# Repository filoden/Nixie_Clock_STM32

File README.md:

# Nixie_Clock_STM32

An STM32-based **Nixie-tube alarm clock** (HH:MM) with audio, SD storage, and a custom enclosure. 
Repository still in developement.

> ⚠️ **High Voltage Warning**
> Nixie tubes require a high-voltage supply (~170VDC for IN-12 used in this project). Basic HV safety knowledge is necessary to avoid injury and or death.

---

## Project Snapshot

**Design tools:** KiCad (PCB), STM32CubeMX / STM32CubeIDE (firmware), SolidWorks (enclosure)

**Repo structure**
- `Current Iteration/` – active hardware + firmware
  - `Current Iteration/Enclosure`
  - `Current Iteration/STM32 Project Files and Code`
  - `Current Iteration/Schematic Layout & PCB`
- `Old_Versions/` – previous spins / archived work

---

## Features

### Hardware / Electronics (status)
**In development**
- low power / battery-power mode
- Oscillator bring-up / stability checks

**Tested (prototype version)**
- Capacitive touch input

**Finalized**
- I2S audio communication
- 5V → 12V boost 
- SPI / I2C communication
- SD Card Interface
- Rotary encoders
- 5V → 3.3V LDO
- Audio output: driving a 4Ω speaker through the MAX98567A (except for bulk cap)
- SD audio file reading

---

## Hardware Overview (high level)

- **MCU:** STM32G0B1RETx6
- **UX/UI:** rotary encoder(s) (One encouder includes a push button), capacitive touch
- **Timekeeping:** STM32 RTC + external LSE oscillator
- **Storage:** microSD over SPI (FatFs)
- **Audio:** I2S to class-D amp (MAX98567A) → 4Ω speaker
- **Driving Nixie Tubes** STM MCU drives serial into a 12V level shifter which drives HV5622PG chips. These chips switch the tubes using an external 170V DC source.
- **Capacitive touch senor** Conductive edge banding surrounds large portions of controller. CAP1206 IC interprets changes in banding capacitance and communicates over I2C to MCU.
- **Power:**
  - USB-C 5V input (mechanical + ESD considerations)
  - 5V enters Linear low-dropout regulator -> 3.3V 
  - 3.3V rail for logic
  - HV rail for Nixie tubes (external boost converter)
  - Battery backup is used for logic, oscillator, amplifier, and capacitive touch sensor in the event of 5V loss
  - Battery and 3.3V power is controlled using NID5100, low-forward voltage drop diodes.
### Schematic Preview

### Block Diagram

#### Notes:
- All Power lines are written in red text
- Arrow direction denotes either flow of power or data (although JTAG should be bidirectional)
- Ground for IN12 Tubes is omitted
---

## Firmware 
### Build / Flash 
1. Open the firmware project in **STM32CubeIDE**.
2. Confirm CubeMX-generated peripherals match the board wiring (SPI for SD, I2S for audio, GPIO/EXTI for inputs). Make sure to include separate driver files for FATFS (Provided by CubeMX). 
4. Build + flash via **ST-LINK**.
5. To avoid frustration, bring-up in this order:
### Firmware Development (Status):
### Integration:
**1. UI FSM**
- UI is structured as an FSM. Programmatically each input will trigger a user-input function for each respective input (knob A turns CC, knob B turns C, etc.. Each function consists of a long switch case which maps the appropriate response to an input for a given state. Relevant code is in UserInterface source and header files. FSM can be seen below.

**Notes to come:**

**2. DMA music playing**

**3. SD card interface**

**4. Capacitive touch sensor**

**5. Music FIle Parsing**

### In development:

**6. Nixie driver control logic**

- Nixie tubes require 170VDC switching. Thankfully, Many old display tubes and other vintage electronics require high voltage DC. Since there is still demand for this technology an old (relatively speaking) serial to parallel high voltage switching IC known as the HV5622PG is still in production. This $8 chip can handle up to 250VDC and requires a ridiculous 12V logic level. The Nixie driver control logic tells this chip which digits to turn on. Importantly, it must also make sure that no more than one digit is driven at a time, as this can easily destroy the tube. Additionally, it is necesary to include PWM control to allow for dimming, and to be easily accessible by other parts of the code.
- Requirements: 
  - Checks to ensure there is no double digit driving
  - Dimming Control
  - Simple function call

**7. Low-Power (Blackout) Handling**

Requirements:
  - Set Pins to LOW (Remove any Pullups as well): Nixie Driving GPIO, JTAG, SD_CARD, CAP1206, knobs B/C
  - Following Interfaces to remain as normal: MAX98357A
  - Sense Power-outage via ST pin on NID5100
  - Be able to play low power alarm song stored solely in on-chip memory

**8. New external LSE with RTC implementation**

Requirements:
  - Initialization
  - Maintain RTC control through momentary resets
  - Calibration (?)
---

## PCB Development
Current version consists of a single main board with three separate smaller boards (separated by user) for the rotary encoder circuitry.
- **V1 PCB:** learning spin (many layout mistakes)
- **V2 PCB:** More fully built out, includes all relevent IO.
- **V3 PCB:** pending completion of wiring/programming development - most up to date version located in current iteration. 
### To-do
- External LSE oscillator testing
- Add AA discharge protection
- Connext NCH6100HV Directly to 5V rail instead of 12V
- Much more
### PCB Preview
**V3 PCB:**
 
---

## Enclosure Development

### Current plan
- Mostly **wood** enclosure in **two glued halves**
- Two halves are **mostly symmetric** and CNC-machinable from a single board  
  - Best results: mill one thick piece and split for mirrored grain (book-matching)
- **Front + back edges:** laser-cut **aluminum edge banding** (strength + aesthetics), glued in place
- **Back plate:** thicker aluminum for rotary encoders + USB-C inlet
- **Front plate:** 1/8" glass (waterjet preferred; hand-fab possible) with a grey tint

### To-do
- Vector files: back plate, glass face, edge banding
- Finalize BOM
- Investigate use of waterjet for glass face
### Enclosure Preview

---

## BOM
- PCB BOM currently matches latest revision
- Enclosure BOM is out of date

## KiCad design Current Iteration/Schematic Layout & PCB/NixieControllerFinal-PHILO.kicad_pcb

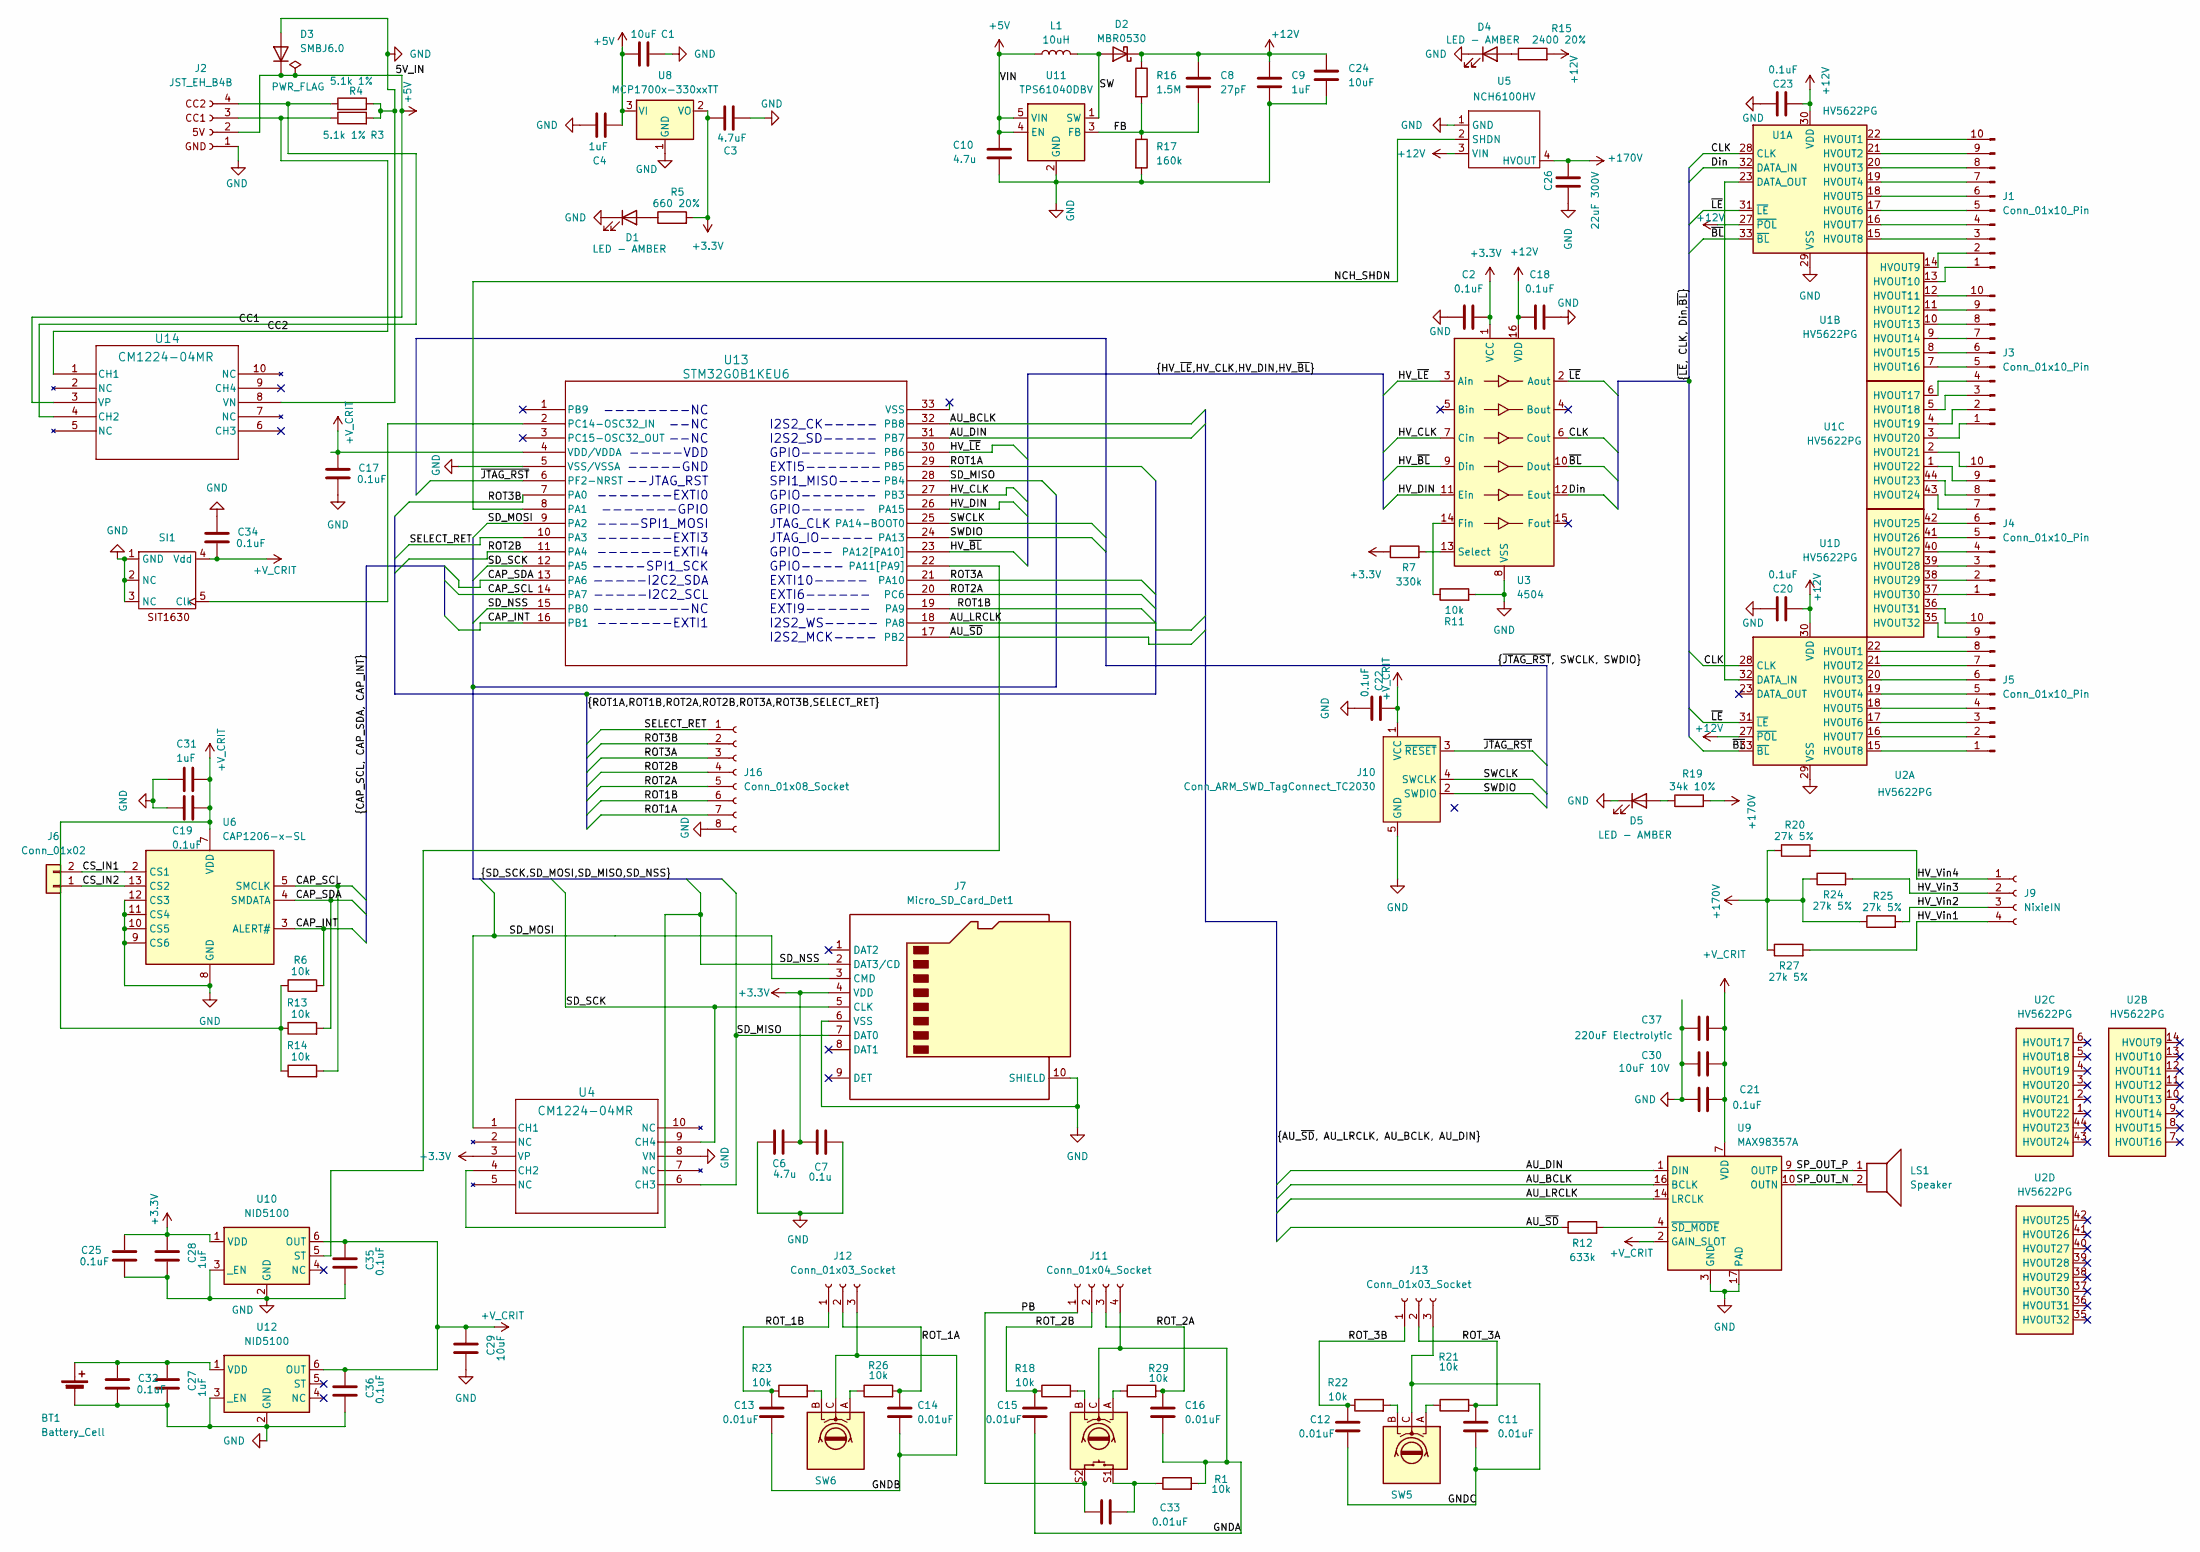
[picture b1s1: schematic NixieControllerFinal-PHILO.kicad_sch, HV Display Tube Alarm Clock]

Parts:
BT1: Battery_Cell; JST_EH_B2B-EH-A_1x02_P2.50mm_Vertical
C1, C24: 10uF; C_0805_2012Metric_Pad1.18x1.45mm_HandSolder
C2, C17, C18, C20, C21, C23, C25, C32, C35, C36: 0.1uF; C_0603_1608Metric_Pad1.08x0.95mm_HandSolder
C3: 4.7uF; C_0805_2012Metric_Pad1.18x1.45mm_HandSolder
C4, C9, C27, C28, C31: 1uF; C_0805_2012Metric_Pad1.18x1.45mm_HandSolder
C6, C10: 4.7u; C_0805_2012Metric_Pad1.18x1.45mm_HandSolder
C7: 0.1u; C_0603_1608Metric_Pad1.08x0.95mm_HandSolder
C8: 27pF; C_0603_1608Metric_Pad1.08x0.95mm_HandSolder
C11, C12, C13, C14, C15, C16, C33: 0.01uF; C_0805_2012Metric_Pad1.18x1.45mm_HandSolder
C19, C22, C34: 0.1uF; C_0805_2012Metric_Pad1.18x1.45mm_HandSolder
C26: 22uF 300V; CP_Radial_D8.0mm_P3.50mm
C29: 10uF; C_1206_3216Metric_Pad1.33x1.80mm_HandSolder
C30: 10uF 10V; C_0603_1608Metric_Pad1.08x0.95mm_HandSolder
C37: 220uF Electrolytic; CP_Radial_D5.0mm_P2.00mm
D1, D4, D5: 150060AS75000; LED_0603_1608Metric_Pad1.05x0.95mm_HandSolder
D2: MBR0530; D_SOD-123
D3: SMBJ6.0; D_SMB
J1, J3, J4, J5: Conn_01x10_Pin; JST_SH_BM10B-SRSS-TB_1x10-1MP_P1.00mm_Vertical
J2: JST_EH_B4B; JST_EH_B4B-EH-A_1x04_P2.50mm_Vertical
J6: Conn_01x02; JST_PH_B2B-PH-K_1x02_P2.00mm_Vertical
J7: Micro_SD_Card_Det1; microSD_HC_Molex_104031-0811
J9: NixieIN; JST_SH_BM04B-SRSS-TB_1x04-1MP_P1.00mm_Vertical
J10: Conn_ARM_SWD_TagConnect_TC2030; PinHeader_1x05_P2.54mm_Vertical
J11: Conn_01x04_Socket; JST_SH_BM04B-SRSS-TB_1x04-1MP_P1.00mm_Vertical
J12, J13: Conn_01x03_Socket; JST_SH_BM03B-SRSS-TB_1x03-1MP_P1.00mm_Vertical
J16: Conn_01x08_Socket; JST_SH_BM08B-SRSS-TB_1x08-1MP_P1.00mm_Vertical
L1: 10uH; L_0805_2012Metric_Pad1.05x1.20mm_HandSolder
LS1: Speaker; JST_PH_B2B-PH-K_1x02_P2.00mm_Vertical
R1, R6, R11, R13, R14, R18, R21, R22, R23, R26, R29: 10k; R_0805_2012Metric_Pad1.20x1.40mm_HandSolder
R3, R4: 5.1k 1%; R_0805_2012Metric_Pad1.20x1.40mm_HandSolder
R5: 660 20%; R_0805_2012Metric_Pad1.20x1.40mm_HandSolder
R7: 330k; R_0805_2012Metric_Pad1.20x1.40mm_HandSolder
R12: 633k; R_0805_2012Metric_Pad1.20x1.40mm_HandSolder
R15: 2400 20%; R_0805_2012Metric_Pad1.20x1.40mm_HandSolder
R16: 1.5M; R_0603_1608Metric_Pad0.98x0.95mm_HandSolder
R17: 160k; R_0603_1608Metric_Pad0.98x0.95mm_HandSolder
R19: 34k 10%; R_1206_3216Metric_Pad1.30x1.75mm_HandSolder
R20, R24, R25, R27: 27k 5%; R_0805_2012Metric_Pad1.20x1.40mm_HandSolder
SI1: SOT-23-5_HandSoldering
SW1, SW5, SW6: RotaryEncoder_Bourns_Vertical_PEC12R-3x17F-Sxxxx
U1, U2: HV5622PG; PQFP-44_10x10mm_P0.8mm
U3: 4504; SOIC-16_ONS
U4, U14: CM1224-04MR; TSSOP-10_3x3mm_P0.5mm
U5: NCH6100HV; JST_EH_B4B-EH-A_1x04_P2.50mm_Vertical
U6: CAP1206-x-SL; SOIC-14_3.9x8.7mm_P1.27mm
U8: MCP1700x-330xxTT; SOT-23
U9: MAX98357A; TQFN-16-1EP_3x3mm_P0.5mm_EP1.23x1.23mm
U10, U12: NID5100; SC-74-6_1.55x2.9mm_P0.95mm
U11: TPS61040DBV; SOT-23-5
U13: STM32G0B1KEU6; UFQFPN-32-1EP_5x5mm_P0.5mm_EP3.5x3.5mm

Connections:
+3.3V: C2.2, C3.1, C6.1, C7.2, C25.1, C28.1, J7.4 (VDD), R5.2, R7.1, U3.1 (VCC), U4.3 (VP), U8.2 (VO), U10.1 (VDD)
+5V: C1.1, C4.1, C10.1, D3.1 (K), J2.2 (5V), L1.1, U8.3 (VI), U11.4 (EN), U11.5 (VIN), U14.3 (VP)
+12V: C8.1, C9.1, C18.1, C20.1, C23.1, C24.1, D2.1 (K), R15.2, R16.1, U1.27 (~POL), U1.30 (VDD), U2.27 (~POL), U2.30 (VDD), U3.16 (VDD), U5.3 (VIN)
+170V: C26.1, R19.2, R20.1, R24.1, R25.1, R27.1, U5.4 (HVOUT)
+V_CRIT: C17.1, C19.1, C21.1, C22.1, C29.1, C30.1, C31.1, C34.2, C35.1, C36.1, C37.1, J10.1 (VCC), R6.1, R13.1, R14.1, SI1.4 (Vdd), U6.7 (VDD), U9.2 (GAIN_SLOT), U9.7 (VDD), U9.8 (VDD), U10.6 (OUT), U12.6 (OUT), U13.4 (VDD/VDDA)
/AU_BCLK: U9.16 (BCLK), U13.32 (PB8)
/AU_DIN: U9.1 (DIN), U13.31 (PB7)
/AU_LRCLK: U9.14 (LRCLK), U13.18 (PA8)
/AU_~SD: R12.1, U13.17 (PB2)
/CAP_INT: R6.2, U6.3 (ALERT#), U13.16 (PB1)
/CAP_SCL: R14.2, U6.5 (SMCLK), U13.14 (PA7)
/CAP_SDA: R13.2, U6.4 (SMDATA), U13.13 (PA6)
/CC1: J2.4 (CC2), R4.1, U14.4 (CH2)
/CC2: J2.3 (CC1), R3.1, U14.1 (CH1)
/CLK: U1.28 (CLK), U2.28 (CLK), U3.6 (Cout)
/CS_IN1: J6.2, U6.2 (CS1)
/CS_IN2: J6.1, U6.13 (CS2)
/Din: U1.32 (DATA_IN), U3.12 (Eout)
/FB: C8.2, R16.2, R17.1, U11.3 (FB)
/GNDA: C15.2, C16.2, J11.4, R1.2, SW1.C
/GNDB: C13.2, C14.2, J12.3, SW6.C
/GNDC: C11.2, C12.2, J13.3, SW5.C
/HV_CLK: U3.7 (Cin), U13.27 (PB3)
/HV_DIN: U3.11 (Ein), U13.26 (PA15)
/HV_Vin1: J9.4, R27.2
/HV_Vin2: J9.3, R25.2
/HV_Vin3: J9.2, R24.2
/HV_Vin4: J9.1, R20.2
/HV_~BL: U3.9 (Din), U13.23 (PA12[PA10])
/HV_~LE: U3.3 (Ain), U13.30 (PB6)
/NCH_SHDN: U5.2 (SHDN), U13.8 (PA1)
/PB: C33.1, J11.1, SW1.S2
/ROT1A: J16.7, U13.29 (PB5)
/ROT1B: J16.6, U13.19 (PA9)
/ROT2A: J16.5, U13.20 (PC6)
/ROT2B: J16.4, U13.11 (PA4)
/ROT3A: J16.3, U13.21 (PA10)
/ROT3B: J16.2, U13.7 (PA0)
/ROT_1A: C14.1, J12.2, R26.2
/ROT_1B: C13.1, J12.1, R23.1
/ROT_2A: C16.1, J11.3, R29.2
/ROT_2B: C15.1, J11.2, R18.1
/ROT_3A: C11.1, J13.2, R21.2
/ROT_3B: C12.1, J13.1, R22.1
/SD_MISO: J7.7 (DAT0), U4.6 (CH3), U13.28 (PB4)
/SD_MOSI: J7.3 (CMD), U4.1 (CH1), U13.9 (PA2)
/SD_NSS: J7.2 (DAT3/CD), U4.4 (CH2), U13.15 (PB0)
/SD_SCK: J7.5 (CLK), U4.9 (CH4), U13.12 (PA5)
/SELECT_RET: J16.1, U13.10 (PA3)
/SP_OUT_N: LS1.2, U9.10 (OUTN)
/SP_OUT_P: LS1.1, U9.9 (OUTP)
/SW: D2.2 (A), L1.2, U11.1 (SW)
/SWCLK: J10.4 (SWCLK), U13.25 (PA14-BOOT0)
/SWDIO: J10.2 (SWDIO), U13.24 (PA13)
/~BL: U1.33 (~BL), U2.33 (~BL), U3.10 (Dout)
/~JTAG_RST: J10.3 (~RESET), U13.6 (PF2-NRST)
/~LE: U1.31 (~LE), U2.31 (~LE), U3.2 (Aout)
GND: BT1.2 (-), C1.2, C2.1, C3.2, C4.2, C6.2, C7.1, C9.2, C10.2, C17.2, C18.2, C19.2, C20.2, C21.2, C22.2, C23.2, C24.2, C25.2, C26.2, C27.2, C28.2, C29.2, C30.2, C31.2, C32.2, C34.1, C35.2, C36.2, C37.2, D1.1 (K), D3.2 (A), D4.1 (K), D5.1 (K), J2.1 (GND), J7.6 (VSS), J7.10 (SHIELD), J10.5 (GND), J16.8, R3.2, R4.2, R11.2, R17.2, SI1.1 (GND), SI1.2 (NC), SI1.3 (NC), U1.29 (VSS), U2.29 (VSS), U3.8 (VSS), U4.8 (VN), U5.1 (GND), U6.8 (GND), U6.9 (CS6), U6.10 (CS5), U6.11 (CS4), U6.12 (CS3), U8.1 (GND), U9.3 (GND), U9.11 (GND), U9.15 (GND), U9.17 (PAD), U10.2 (GND), U10.3 (_EN), U11.2 (GND), U12.2 (GND), U12.3 (_EN), U13.5 (VSS/VSSA), U14.8 (VN)
unnamed: BT1.1 (+), C27.1, C32.1, U12.1 (VDD)
unnamed: C33.2, R1.1, SW1.S1
unnamed: D1.2 (A), R5.1
unnamed: D4.2 (A), R15.1
unnamed: D5.2 (A), R19.1
unnamed: J1.1, U1.13 (HVOUT10)
unnamed: J1.2, U1.14 (HVOUT9)
unnamed: J1.3, U1.15 (HVOUT8)
unnamed: J1.4, U1.16 (HVOUT7)
unnamed: J1.5, U1.17 (HVOUT6)
unnamed: J1.6, U1.18 (HVOUT5)
unnamed: J1.7, U1.19 (HVOUT4)
unnamed: J1.8, U1.20 (HVOUT3)
unnamed: J1.9, U1.21 (HVOUT2)
unnamed: J1.10, U1.22 (HVOUT1)
unnamed: J3.1, U1.3 (HVOUT20)
unnamed: J3.2, U1.4 (HVOUT19)
unnamed: J3.3, U1.5 (HVOUT18)
unnamed: J3.4, U1.6 (HVOUT17)
unnamed: J3.5, U1.7 (HVOUT16)
unnamed: J3.6, U1.8 (HVOUT15)
unnamed: J3.7, U1.9 (HVOUT14)
unnamed: J3.8, U1.10 (HVOUT13)
unnamed: J3.9, U1.11 (HVOUT12)
unnamed: J3.10, U1.12 (HVOUT11)
unnamed: J4.1, U1.37 (HVOUT30)
unnamed: J4.2, U1.38 (HVOUT29)
unnamed: J4.3, U1.39 (HVOUT28)
unnamed: J4.4, U1.40 (HVOUT27)
unnamed: J4.5, U1.41 (HVOUT26)
unnamed: J4.6, U1.42 (HVOUT25)
unnamed: J4.7, U1.43 (HVOUT24)
unnamed: J4.8, U1.44 (HVOUT23)
unnamed: J4.9, U1.1 (HVOUT22)
unnamed: J4.10, U1.2 (HVOUT21)
unnamed: J5.1, U2.15 (HVOUT8)
unnamed: J5.2, U2.16 (HVOUT7)
unnamed: J5.3, U2.17 (HVOUT6)
unnamed: J5.4, U2.18 (HVOUT5)
unnamed: J5.5, U2.19 (HVOUT4)
unnamed: J5.6, U2.20 (HVOUT3)
unnamed: J5.7, U2.21 (HVOUT2)
unnamed: J5.8, U2.22 (HVOUT1)
unnamed: J5.9, U1.35 (HVOUT32)
unnamed: J5.10, U1.36 (HVOUT31)
unnamed: R18.2, SW1.B
unnamed: R21.1, SW5.A
unnamed: R22.2, SW5.B
unnamed: R23.2, SW6.B
unnamed: R26.1, SW6.A
unnamed: R29.1, SW1.A
unnamed: SI1.5 (Clk), U13.2 (PC14-OSC32_IN)
unnamed: U1.23 (DATA_OUT), U2.32 (DATA_IN)
unnamed: R11.1, U3.14 (Fin)
unnamed: R7.2, U3.13 (Select)
unnamed: R12.2, U9.4 (~SD_MODE)
unnamed: U10.5 (ST), U13.22 (PA11[PA9])

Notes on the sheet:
--------NC --NC --NC -----VDD -----GND --JTAG_RST -------EXTI0 -------GPIO ----SPI1_MOSI -------EXTI3 -------EXTI4 -----SPI1_SCK -----I2C2_SDA -----I2C2_SCL ---------NC -------EXTI1
I2S2_CK----- I2S2_SD----- GPIO------- EXTI5------- SPI1_MISO---- GPIO------- GPIO------ JTAG_CLK JTAG_IO----- GPIO--- GPIO---- EXTI10----- EXTI6------ EXTI9------ I2S2_WS----- I2S2_MCK----

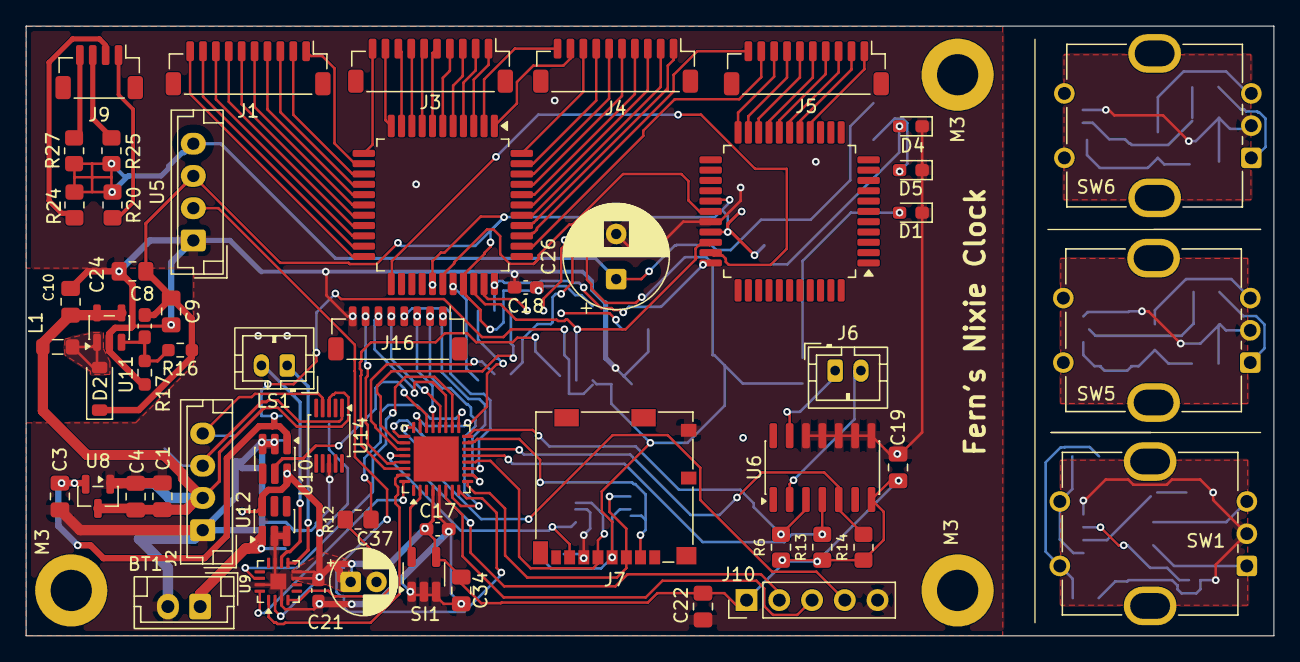
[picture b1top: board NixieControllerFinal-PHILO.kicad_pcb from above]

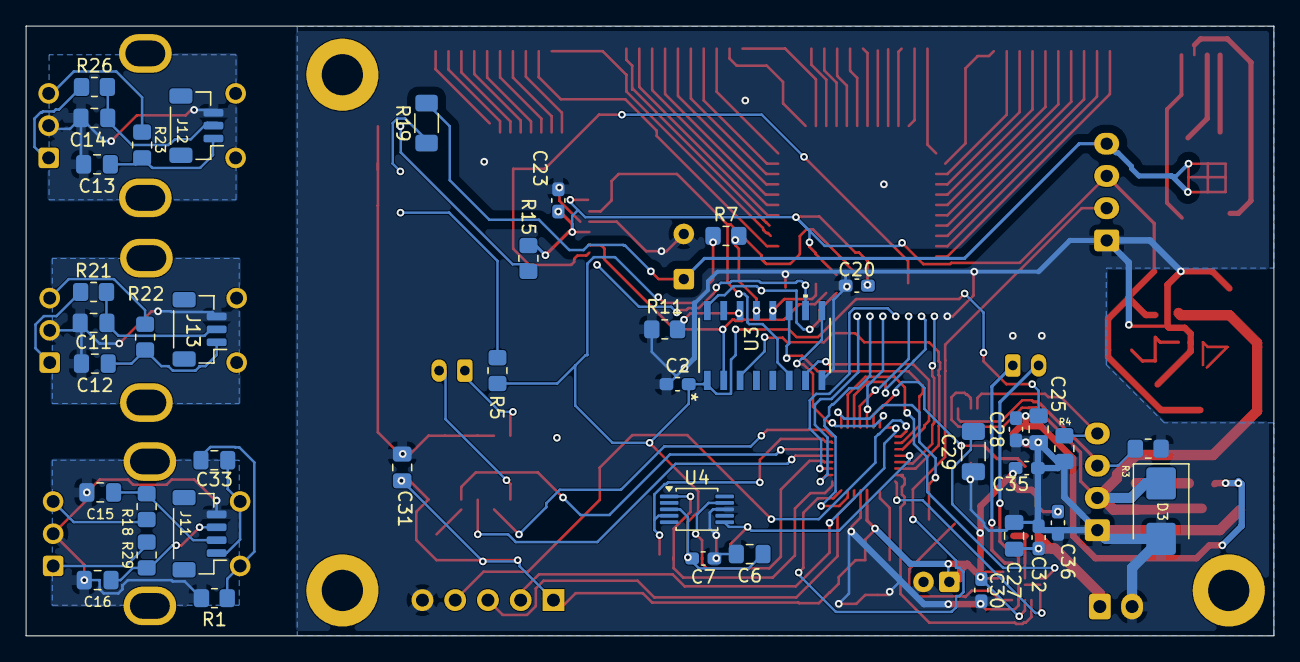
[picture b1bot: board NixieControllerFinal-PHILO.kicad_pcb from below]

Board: 2 copper layers, 96.8 x 47.3 mm, 98 parts (41 on the bottom side), 115 nets.

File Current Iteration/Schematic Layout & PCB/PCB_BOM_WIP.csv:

"Reference","Qty","Value","DNP","Exclude from BOM","Exclude from Board","Footprint","Datasheet"
"BT1","1","Battery_Cell","","","","Connector_JST:JST_EH_B2B-EH-A_1x02_P2.50mm_Vertical","~"
"C1,C29,C30","3","10uF","","","","Capacitor_SMD:C_0805_2012Metric_Pad1.18x1.45mm_HandSolder","~"
"C2,C17,C18,C19,C21,C22,C25","7","0.1uF","","","","Capacitor_SMD:C_0805_2012Metric_Pad1.18x1.45mm_HandSolder","~"
"C3","1","4.7uF","","","","Capacitor_SMD:C_0805_2012Metric_Pad1.18x1.45mm_HandSolder","~"
"C4,C9,C27,C28,C31","5","1uF","","","","Capacitor_SMD:C_0805_2012Metric_Pad1.18x1.45mm_HandSolder","~"
"C5","1","220uF","","","","Capacitor_SMD:C_1206_3216Metric_Pad1.33x1.80mm_HandSolder","~"
"C6","1","4.7u","","","","Capacitor_SMD:C_1206_3216Metric_Pad1.33x1.80mm_HandSolder","~"
"C7","1","0.1u","","","","Capacitor_SMD:C_0805_2012Metric_Pad1.18x1.45mm_HandSolder","~"
"C8","1","27pF","","","","Capacitor_SMD:C_0805_2012Metric_Pad1.18x1.45mm_HandSolder","~"
"C10","1","4.7u","","","","Capacitor_SMD:C_0805_2012Metric_Pad1.18x1.45mm_HandSolder","~"
"C11,C12,C13,C14,C15,C16,C33","7","0.01uF","","","","Capacitor_SMD:C_0805_2012Metric_Pad1.18x1.45mm_HandSolder","~"
"C20,C23","2","0.1uF","","","","Capacitor_SMD:C_1808_4520Metric_Pad1.72x2.30mm_HandSolder","~"
"C24,C32","2","10uF","","","","Capacitor_SMD:C_1206_3216Metric_Pad1.33x1.80mm_HandSolder","~"
"C26","1","22uF 300V","","","","Capacitor_THT:CP_Radial_D8.0mm_P3.50mm","~"
"D1","1","3.3V+","","","","LED_SMD:LED_0603_1608Metric_Pad1.05x0.95mm_HandSolder","~"
"D2","1","MBR0530","","","","Diode_SMD:D_SOD-123","http://www.mccsemi.com/up_pdf/MBR0520~MBR0580(SOD123).pdf"
"D3","1","SMBJ6.0","","","","Diode_SMD:D_SMB","~"
"D4","1","12V+","","","","LED_SMD:LED_0603_1608Metric_Pad1.05x0.95mm_HandSolder","~"
"D5","1","170V+","","","","LED_SMD:LED_0603_1608Metric_Pad1.05x0.95mm_HandSolder","~"
"J1,J3,J4,J5","4","Conn_01x10_Pin","","","","Connector_JST:JST_SH_BM10B-SRSS-TB_1x10-1MP_P1.00mm_Vertical","~"
"J2","1","Conn_01x02","","","","","~"
"J6","1","Conn_01x02","","","","Connector_JST:JST_EH_B2B-EH-A_1x02_P2.50mm_Vertical","~"
"J7","1","Micro_SD_Card_Det1","","","","footprints:MEM2061-01-188-00-A_GCT","https://datasheet.lcsc.com/lcsc/2110151630_XKB-Connectivity-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"
"J8","1","Conn_ARM_JTAG_SWD_10","","","","Connector_JST:JST_SH_BM05B-SRSS-TB_1x05-1MP_P1.00mm_Vertical","http://infocenter.arm.com/help/topic/com.arm.doc.ddi0314h/DD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"
"J9","1","NixieIN","","","","Connector_JST:JST_SH_BM04B-SRSS-TB_1x04-1MP_P1.00mm_Vertical","~"
"J10","1","2480803-1","","","","Connector_USB:24808031","https://www.te.com/de/product-2480803-1.datasheet.pdf"
"J11","1","Conn_01x04_Socket","","","","Connector_JST:JST_SH_BM04B-SRSS-TB_1x04-1MP_P1.00mm_Vertical","~"
"J12,J13","2","Conn_01x03_Socket","","","","Connector_JST:JST_SH_BM03B-SRSS-TB_1x03-1MP_P1.00mm_Vertical","~"
"J15","1","Conn_01x02_Socket","","","","Connector_JST:JST_EH_B2B-EH-A_1x02_P2.50mm_Vertical","~"
"J16","1","Conn_01x08_Socket","","","","Connector_JST:JST_SH_BM08B-SRSS-TB_1x08-1MP_P1.00mm_Vertical","~"
"L1","1","10uH","","","","Inductor_SMD:L_0805_2012Metric_Pad1.05x1.20mm_HandSolder","~"
"LS1","1","Speaker","","","","Connector_JST:JST_PH_B2B-PH-K_1x02_P2.00mm_Vertical","~"
"R1,R6,R11,R13,R14,R18,R21,R22,R23,R26,R29","11","10k","","","","Resistor_SMD:R_0805_2012Metric_Pad1.20x1.40mm_HandSolder","~"
"R2","1","35K","","","","Resistor_SMD:R_0805_2012Metric_Pad1.20x1.40mm_HandSolder","~"
"R3,R4","2","5.1k 1%","","","","Resistor_SMD:R_0805_2012Metric_Pad1.20x1.40mm_HandSolder","~"
"R5","1","86 20%","","","","Resistor_SMD:R_0805_2012Metric_Pad1.20x1.40mm_HandSolder","~"
"R7","1","330k","","","","Resistor_SMD:R_0805_2012Metric_Pad1.20x1.40mm_HandSolder","~"
"R12","1","633k","","","","Resistor_SMD:R_0805_2012Metric_Pad1.20x1.40mm_HandSolder","~"
"R15","1","670 20%","","","","Resistor_SMD:R_0805_2012Metric_Pad1.20x1.40mm_HandSolder","~"
"R16","1","1.5M","","","","Resistor_SMD:R_0805_2012Metric_Pad1.20x1.40mm_HandSolder","~"
"R17","1","160k","","","","Resistor_SMD:R_0805_2012Metric_Pad1.20x1.40mm_HandSolder","~"
"R19","1","11200 20%","","","","Resistor_SMD:R_0805_2012Metric_Pad1.20x1.40mm_HandSolder","~"
"R20,R24,R25,R27","4","27k 5%","","","","Resistor_SMD:R_0805_2012Metric_Pad1.20x1.40mm_HandSolder","~"
"SW1,SW5,SW6","3","~","","","","Rotary_Encoder:RotaryEncoder_Bourns_Vertical_PEC12R-3x17F-Sxxxx","kicad-embed://PEC11J.pdf,kicad-embed://pec16.pdf"
"U1,U2","2","HV5622PG","","","","Package_QFP:PQFP-44_10x10mm_P0.8mm","https://ww1.microchip.com/downloads/aemDocuments/documents/O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"
"U3","1","4504","","","","footprints:SOIC-16_ONS","http://www.ti.com/lit/ds/symlink/cd4504b.pdf"
"U4,U14","2","CM1224-04MR","","","","Package_SO:MSOP-10_3x3mm_P0.5mm","CM1224-04MR"
"U5","1","NCH6100HV","","","","Connector_JST:JST_EH_B4B-EH-A_1x04_P2.50mm_Vertical","kicad-embed://NIXIE-Power-Supply-Datasheet-EN-v1.0.0.pdf"
"U6","1","CAP1206-x-SL","","","","Package_SO:SOIC-14_3.9x8.7mm_P1.27mm","http://ww1.microchip.com/downloads/en/DeviceDoc/00001567B.pdf"
"U7,U10","2","NID1100","","","","Package_TO_SOT_SMD:SC-74A-5_1.55x2.9mm_P0.95mm","https://assets.nexperia.com/documents/data-sheet/NID1100.pdf"
"U8","1","MCP1700x-330xxTT","","","","Package_TO_SOT_SMD:SOT-23","http://ww1.microchip.com/downloads/en/DeviceDoc/20001826D.pdf"
"U9","1","MAX98357A","","","","Package_DFN_QFN:TQFN-16-1EP_3x3mm_P0.5mm_EP1.23x1.23mm","https://www.analog.com/media/en/technical-documentation/data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"
"U11","1","TPS61040DBV","","","","Package_TO_SOT_SMD:SOT-23-5","http://www.ti.com/lit/ds/symlink/tps61040.pdf"
"U13","1","STM32G0B1KEU6","","","","Package_DFN_QFN:UFQFPN-32-1EP_5x5mm_P0.5mm_EP3.5x3.5mm","https://www.st.com/resource/en/datasheet/stm32g0b1cc.pdf"

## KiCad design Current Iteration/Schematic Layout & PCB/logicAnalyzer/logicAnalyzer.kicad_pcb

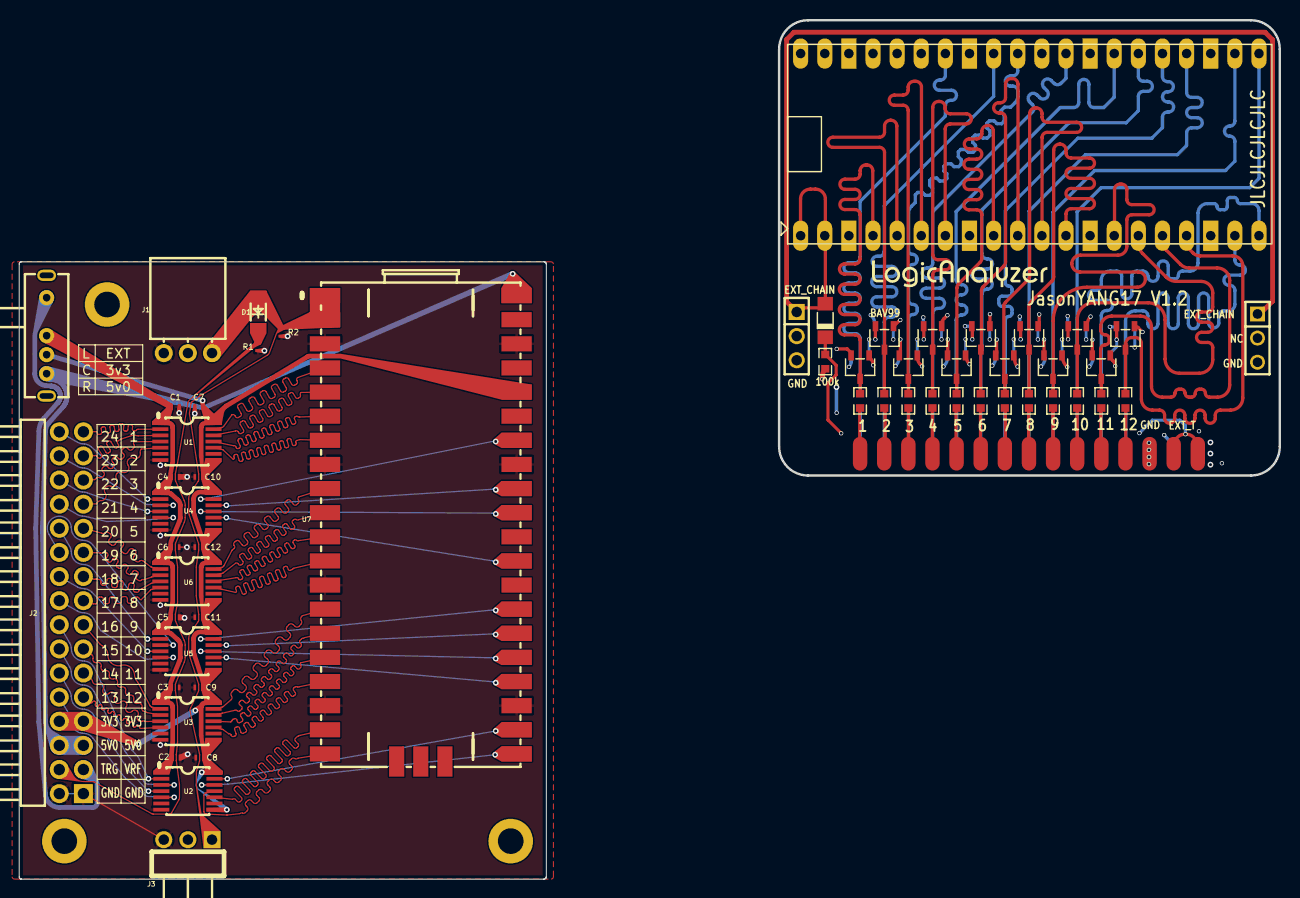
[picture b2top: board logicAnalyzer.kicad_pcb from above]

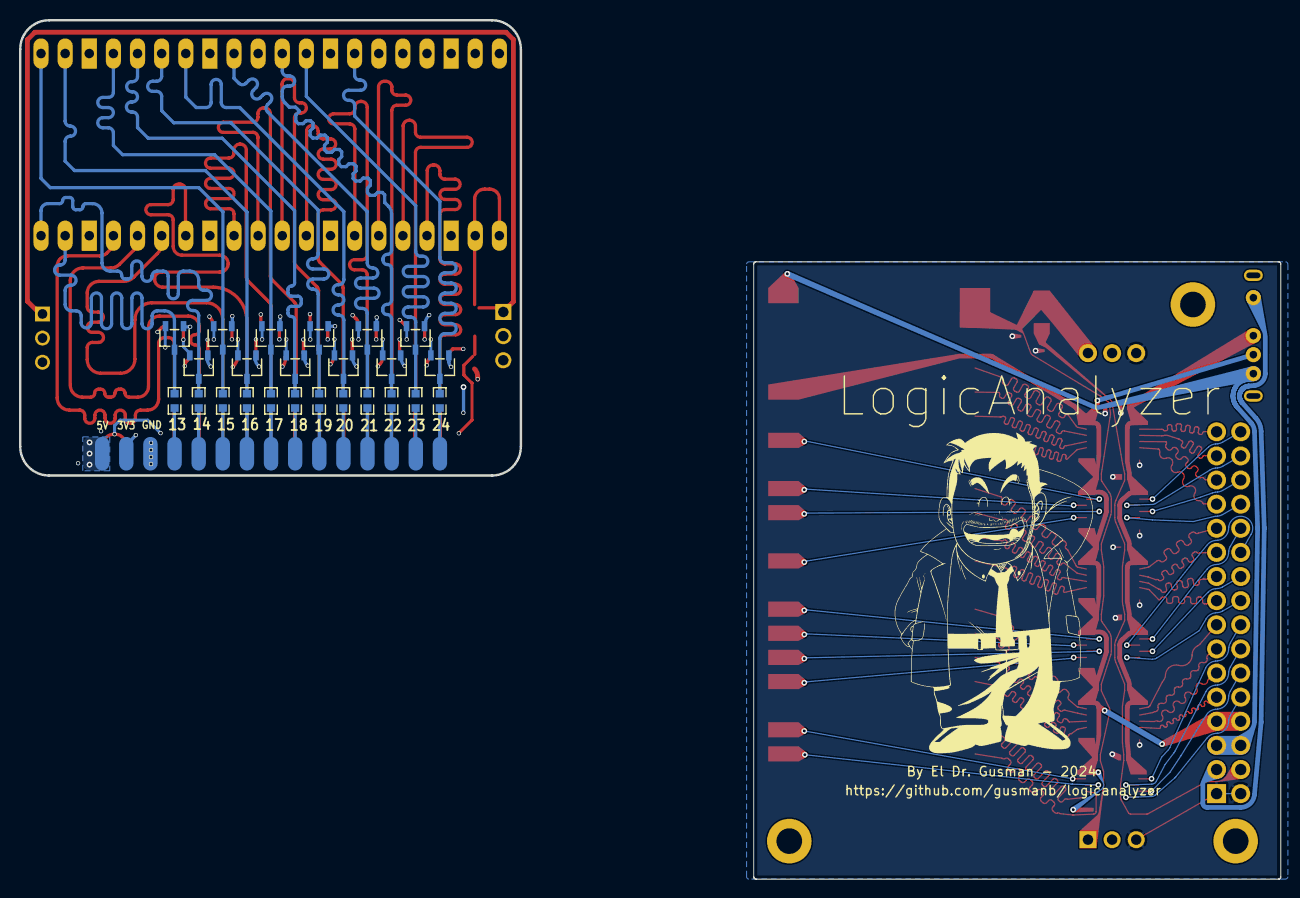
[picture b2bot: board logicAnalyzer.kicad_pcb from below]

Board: 4 copper layers, 132.7 x 90.4 mm, 80 parts (24 on the bottom side), 106 nets.

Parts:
C1: 100n; Pkg0402_3
C2: 100n; Pkg0402
C3: 100n; Pkg0402_12
C4: 100n; Pkg0402_6
C5: 100n; Pkg0402_7
C6: 100n; Pkg0402_9
C7: 100n; Pkg0402_5
C8: 100n; Pkg0402_8
C9: 100n; Pkg0402_10
C10: 100n; Pkg0402_11
C11: 100n; Pkg0402_1
C12: 100n; Pkg0402_13
D1: LL4148; LL_34_L3_5_W1_5_RD
D1#2, D3, D4, D5, D6, D7, D8, D9, D10, D11, D12, D13, D14, D15, D16, D17, D18, D19, D20, D21, D22, D23, D24, D25: SOT-23-3_L2.9-W1.6-P1.90-LS2.8-BR
D2: SOD-80_L3.5-W1.5-RD
H1: HDR-TH_3P-P2.54-V-F
H2: HDR-TH_3P-P2.54-V-M
J1: PM254-1-03-W-8.5; HDR_TH_3P_P2_54_H_F_W10_0_N
J2: C97095; HDR_TH_32P_P2_54_H_M_R2_C16_S2_54_1
J3: DZ254W-11-03-65; HDR_TH_3P_P2_54_H_M_W10_0
R1: 100K; Pkg0402_4
R1#2, R2, R3, R4, R5, R6, R7, R8, R9, R10, R11, R12, R13, R14, R15, R16, R17, R18, R19, R20, R21, R22, R23, R24, R25: R0603
R2#2: 8K2; Pkg0402_2
S1: SK-13D01-G030; SW_TH_SK_13D01_G030
U1: TXU0104PWR; TSSOP_14_L5_0_W4_4_P0_65_LS6_4_BL_5
U2: 树莓派pico多层
U2#2: TXU0104PWR; TSSOP_14_L5_0_W4_4_P0_65_LS6_4_BL_4
U3: TXU0104PWR; TSSOP_14_L5_0_W4_4_P0_65_LS6_4_BL
U3#2: HDR-TH_30P-P2.54-V-F-R2-C15-S2.54-A
U4: TXU0104PWR; TSSOP_14_L5_0_W4_4_P0_65_LS6_4_BL_3
U5: TXU0104PWR; TSSOP_14_L5_0_W4_4_P0_65_LS6_4_BL_1
U6: TXU0104PWR; TSSOP_14_L5_0_W4_4_P0_65_LS6_4_BL_2
U7: PICO; COMM_SMD_L51_0_W21_0_P2_54_SC0916

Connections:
$1N6412: R2.2, U3#2.1
$1N6457: R3.2, U3#2.2
$1N6576: R4.2, U3#2.3
$1N6580: R5.2, U3#2.4
$1N6666: R6.2, U3#2.5
$1N6670: R7.2, U3#2.6
$1N6756: R8.2, U3#2.7
$1N6760: R9.2, U3#2.8
$1N6846: R10.2, U3#2.9
$1N6850: R11.2, U3#2.10
$1N6936: R12.2, U3#2.11
$1N6940: R13.2, U3#2.12
$1N7395: R25.1, U3#2.19
$1N7399: R24.1, U3#2.20
$1N7403: R23.1, U3#2.21
$1N7407: R22.1, U3#2.22
$1N7411: R21.1, U3#2.23
$1N7415: R20.1, U3#2.24
$1N7419: R19.1, U3#2.25
$1N7423: R18.1, U3#2.26
$1N7427: R17.1, U3#2.27
$1N7431: R16.1, U3#2.28
$1N7435: R15.1, U3#2.29
$1N7439: R14.1, U3#2.30
+3.3V: D1#2.2, D3.2, D4.2, D5.2, D6.2, D7.2, D8.2, D9.2, D10.2, D11.2, D12.2, D13.2, D14.2, D15.2, D16.2, D17.2, D18.2, D19.2, D20.2, D21.2, D22.2, D23.2, D24.2, D25.2, U2.36, U3#2.17
+5V: U2.40, U3#2.16
CHAN_0: D25.3, R2.1, U2.4
CHAN_1: D1#2.3, R3.1, U2.5
CHAN_2: D3.3, R4.1, U2.6
CHAN_3: D4.3, R5.1, U2.7
CHAN_4: D5.3, R6.1, U2.9
CHAN_5: D6.3, R7.1, U2.10
CHAN_6: D7.3, R8.1, U2.11
CHAN_7: D8.3, R9.1, U2.12
CHAN_8: D9.3, R10.1, U2.14
CHAN_9: D10.3, R11.1, U2.15
CHAN_10: D11.3, R12.1, U2.16
CHAN_11: D12.3, R13.1, U2.17
CHAN_12: D13.3, R25.2, U2.19
CHAN_13: D14.3, R24.2, U2.20
CHAN_14: D15.3, R23.2, U2.21
CHAN_15: D16.3, R22.2, U2.22
CHAN_16: D17.3, R21.2, U2.24
CHAN_17: D18.3, R20.2, U2.25
CHAN_18: D19.3, R19.2, U2.26
CHAN_19: D20.3, R18.2, U2.27
CHAN_20: D21.3, R17.2, U2.29
CHAN_21: D22.3, R16.2, U2.31
CHAN_22: D23.3, R15.2, U2.32
CHAN_23: D24.3, R14.2, U2.34
DIN1: J2.31, U1.2
DIN2: J2.29, U1.3
DIN3: J2.27, U1.4
DIN4: J2.25, U1.5
DIN5: J2.23, U6.2
DIN6: J2.21, U6.3
DIN7: J2.19, U6.4
DIN8: J2.17, U6.5
DIN9: J2.15, U3.2
DIN10: J2.13, U3.3
DIN11: J2.11, U3.4
DIN12: J2.9, U3.5
DIN13: J2.10, U2#2.5
DIN14: J2.12, U2#2.4
DIN15: J2.14, U2#2.3
DIN16: J2.16, U2#2.2
DIN17: J2.18, U5.5
DIN18: J2.20, U5.4
DIN19: J2.22, U5.3
DIN20: J2.24, U5.2
DIN21: J2.26, U4.5
DIN22: J2.28, U4.4
DIN23: J2.30, U4.3
DIN24: J2.32, U4.2
DOUT1: U1.13, U7.4
DOUT2: U1.12, U7.5
DOUT3: U1.11, U7.6
DOUT4: U1.10, U7.7
DOUT5: U6.13, U7.9
DOUT6: U6.12, U7.10
DOUT7: U6.11, U7.11
DOUT8: U6.10, U7.12
DOUT9: U3.13, U7.14
DOUT10: U3.12, U7.15
DOUT11: U3.11, U7.16
DOUT12: U3.10, U7.17
DOUT13: U2#2.10, U7.19
DOUT14: U2#2.11, U7.20
DOUT15: U2#2.12, U7.21
DOUT16: U2#2.13, U7.22
DOUT17: U5.10, U7.24
DOUT18: U5.11, U7.25
DOUT19: U5.12, U7.26
DOUT20: U5.13, U7.27
DOUT21: U4.10, U7.29
DOUT22: U4.11, U7.31
DOUT23: U4.12, U7.32
DOUT24: U4.13, U7.34
EXT_CHAIN: D1.2, D2.2, H1.1, H2.1, J1.1, J3.1, R2#2.1, U2.1, U2.2, U7.1, U7.2
EXT_T: D2.1, R1#2.2, U3#2.14, U3#2.15
EXT_TRIG: D1.1, J2.4, R1.1
EXT_VREF: J2.3, S1.1
GND: C1.1, C2.1, C3.1, C4.1, C5.1, C6.1, C7.1, C8.1, C9.1, C10.1, C11.1, C12.1, D1#2.1, D3.1, D4.1, D5.1, D6.1, D7.1, D8.1, D9.1, D10.1, D11.1, D12.1, D13.1, D14.1, D15.1, D16.1, D17.1, D18.1, D19.1, D20.1, D21.1, D22.1, D23.1, D24.1, D25.1, H1.3, H2.3, J1.3, J2.1, J2.2, J3.3, R1.2, R1#2.1, R2#2.2, U1.7, U2.3, U2.8, U2.13, U2.18, U2.23, U2.28, U2.38, U2#2.7, U3.7, U3#2.13, U3#2.18, U4.7, U5.7, U6.7, U7.3, U7.8, U7.13, U7.18, U7.23, U7.33, U7.38
POWER_3v3: C7.2, C8.2, C9.2, C10.2, C11.2, C12.2, J2.7, J2.8, S1.3, U1.8, U1.14, U2#2.8, U2#2.14, U3.8, U3.14, U4.8, U4.14, U5.8, U5.14, U6.8, U6.14, U7.36
POWER_5v: J2.5, J2.6, S1.4, U7.40
VREF: C1.2, C2.2, C3.2, C4.2, C5.2, C6.2, S1.2, U1.1, U2#2.1, U3.1, U4.1, U5.1, U6.1

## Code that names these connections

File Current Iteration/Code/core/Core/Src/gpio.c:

/* USER CODE BEGIN Header */
/**
  ******************************************************************************
  * @file    gpio.c
  * @brief   This file provides code for the configuration
  *          of all used GPIO pins.
  ******************************************************************************
  * @attention
  *
  * Copyright (c) 2026 STMicroelectronics.
  * All rights reserved.
  *
  * This software is licensed under terms that can be found in the LICENSE file
  * in the root directory of this software component.
  * If no LICENSE file comes with this software, it is provided AS-IS.
  *
  ******************************************************************************
  */
/* USER CODE END Header */

/* Includes ------------------------------------------------------------------*/
#include "gpio.h"

/* USER CODE BEGIN 0 */

/* USER CODE END 0 */

/*----------------------------------------------------------------------------*/
/* Configure GPIO                                                             */
/*----------------------------------------------------------------------------*/
/* USER CODE BEGIN 1 */

/* USER CODE END 1 */

/** Configure pins as
        * Analog
        * Input
        * Output
        * EVENT_OUT
        * EXTI
     PA5   ------> SPI1_SCK
     PB4   ------> SPI1_MISO
*/
void MX_GPIO_Init(void)
{

  GPIO_InitTypeDef GPIO_InitStruct = {0};

  /* GPIO Ports Clock Enable */
  __HAL_RCC_GPIOC_CLK_ENABLE();
  __HAL_RCC_GPIOF_CLK_ENABLE();
  __HAL_RCC_GPIOA_CLK_ENABLE();
  __HAL_RCC_GPIOB_CLK_ENABLE();
  __HAL_RCC_GPIOD_CLK_ENABLE();

  /*Configure GPIO pin Output Level */
  HAL_GPIO_WritePin(GPIOA, GPIO_PIN_1|GPIO_PIN_15, GPIO_PIN_RESET);

  /*Configure GPIO pin Output Level */
  HAL_GPIO_WritePin(GPIOB, GPIO_PIN_2|GPIO_PIN_3|GPIO_PIN_6, GPIO_PIN_RESET);

  /*Configure GPIO pin : B1_Pin */
  GPIO_InitStruct.Pin = B1_Pin;
  GPIO_InitStruct.Mode = GPIO_MODE_IT_RISING;
  GPIO_InitStruct.Pull = GPIO_NOPULL;
  HAL_GPIO_Init(B1_GPIO_Port, &GPIO_InitStruct);

  /*Configure GPIO pins : PC14 PC15 */
  GPIO_InitStruct.Pin = GPIO_PIN_14|GPIO_PIN_15;
  GPIO_InitStruct.Mode = GPIO_MODE_INPUT;
  GPIO_InitStruct.Pull = GPIO_NOPULL;
  HAL_GPIO_Init(GPIOC, &GPIO_InitStruct);

  /*Configure GPIO pins : PA0 PA9 PA10 */
  GPIO_InitStruct.Pin = GPIO_PIN_0|GPIO_PIN_9|GPIO_PIN_10;
  GPIO_InitStruct.Mode = GPIO_MODE_IT_RISING_FALLING;
  GPIO_InitStruct.Pull = GPIO_PULLUP;
  HAL_GPIO_Init(GPIOA, &GPIO_InitStruct);

  /*Configure GPIO pins : PA1 PA15 */
  GPIO_InitStruct.Pin = GPIO_PIN_1|GPIO_PIN_15;
  GPIO_InitStruct.Mode = GPIO_MODE_OUTPUT_PP;
  GPIO_InitStruct.Pull = GPIO_NOPULL;
  GPIO_InitStruct.Speed = GPIO_SPEED_FREQ_LOW;
  HAL_GPIO_Init(GPIOA, &GPIO_InitStruct);

  /*Configure GPIO pin : PA5 */
  GPIO_InitStruct.Pin = GPIO_PIN_5;
  GPIO_InitStruct.Mode = GPIO_MODE_AF_PP;
  GPIO_InitStruct.Pull = GPIO_NOPULL;
  GPIO_InitStruct.Speed = GPIO_SPEED_FREQ_LOW;
  GPIO_InitStruct.Alternate = GPIO_AF0_SPI1;
  HAL_GPIO_Init(GPIOA, &GPIO_InitStruct);

  /*Configure GPIO pins : PB0 PB9 */
  GPIO_InitStruct.Pin = GPIO_PIN_0|GPIO_PIN_9;
  GPIO_InitStruct.Mode = GPIO_MODE_INPUT;
  GPIO_InitStruct.Pull = GPIO_NOPULL;
  HAL_GPIO_Init(GPIOB, &GPIO_InitStruct);

  /*Configure GPIO pins : PB1 PB5 */
  GPIO_InitStruct.Pin = GPIO_PIN_1|GPIO_PIN_5;
  GPIO_InitStruct.Mode = GPIO_MODE_IT_RISING_FALLING;
  GPIO_InitStruct.Pull = GPIO_PULLUP;
  HAL_GPIO_Init(GPIOB, &GPIO_InitStruct);

  /*Configure GPIO pins : PB2 PB3 PB6 */
  GPIO_InitStruct.Pin = GPIO_PIN_2|GPIO_PIN_3|GPIO_PIN_6;
  GPIO_InitStruct.Mode = GPIO_MODE_OUTPUT_PP;
  GPIO_InitStruct.Pull = GPIO_NOPULL;
  GPIO_InitStruct.Speed = GPIO_SPEED_FREQ_LOW;
  HAL_GPIO_Init(GPIOB, &GPIO_InitStruct);

  /*Configure GPIO pin : PC6 */
  GPIO_InitStruct.Pin = GPIO_PIN_6;
  GPIO_InitStruct.Mode = GPIO_MODE_IT_RISING_FALLING;
  GPIO_InitStruct.Pull = GPIO_PULLUP;
  HAL_GPIO_Init(GPIOC, &GPIO_InitStruct);

  /*Configure GPIO pin : PD3 */
  GPIO_InitStruct.Pin = GPIO_PIN_3;
  GPIO_InitStruct.Mode = GPIO_MODE_IT_RISING_FALLING;
  GPIO_InitStruct.Pull = GPIO_PULLUP;
  HAL_GPIO_Init(GPIOD, &GPIO_InitStruct);

  /*Configure GPIO pin : PB4 */
  GPIO_InitStruct.Pin = GPIO_PIN_4;
  GPIO_InitStruct.Mode = GPIO_MODE_AF_PP;
  GPIO_InitStruct.Pull = GPIO_NOPULL;
  GPIO_InitStruct.Speed = GPIO_SPEED_FREQ_LOW;
  GPIO_InitStruct.Alternate = GPIO_AF0_SPI1;
  HAL_GPIO_Init(GPIOB, &GPIO_InitStruct);

  /* EXTI interrupt init*/
  HAL_NVIC_SetPriority(EXTI0_1_IRQn, 0, 0);
  HAL_NVIC_EnableIRQ(EXTI0_1_IRQn);

  HAL_NVIC_SetPriority(EXTI2_3_IRQn, 0, 0);
  HAL_NVIC_EnableIRQ(EXTI2_3_IRQn);

  HAL_NVIC_SetPriority(EXTI4_15_IRQn, 0, 0);
  HAL_NVIC_EnableIRQ(EXTI4_15_IRQn);

}

/* USER CODE BEGIN 2 */

/* USER CODE END 2 */

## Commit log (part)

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2026-01-30 Enhance README with project details and development status
    Expanded the README to include detailed sections on wiring/programming, PCB, and enclosure development.
2026-01-30 Add OldVersions directory with .gitkeep file
2026-02-04 Repo cleanup and code update
2026-02-10 Working SPI protocol, SD reading, OS development
2026-02-11 readme update and schematic cleanup
2026-02-12 Organization and CAD files
2026-02-12 Organization and full project files
2026-02-12 Corrupted project files fix
2026-02-12 Todo
2026-02-12 Update BOM status in README
    Clarified the status of the BOM in the README.
2026-06-13 repo refresh
2026-06-21 Latest PCB revision
2026-06-21 Update Todo list with oscillator/RTC module
    Added oscillator/RTC module incorporation to PCB and schematic todos.
2026-06-21 Rename PCB_BOM_WIP).csv to PCB_BOM_WIP.csv
2026-06-21 Fix formatting in Enclosure_BOM_WIP.csv
2026-06-21 Update Todo list with new tasks and remove completed ones
2026-06-21 Revise README for clarity and additional details
    Updated README.md to improve clarity and detail on project components and safety warnings.
2026-06-23 Addign Block Diagram
2026-06-23 Adding Block Diagram
2026-06-23 Enhance README with schematic and enclosure previews
    Added schematic, block diagram, PCB, and enclosure previews to README.
